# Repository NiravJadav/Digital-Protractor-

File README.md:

# Digital-Protractor-
What if Your Ruler Scale converted in to Protractor .....  This Project is all about convert an ordinary ruler in to Smart Ruler having a extra feature of measurement of Angle.

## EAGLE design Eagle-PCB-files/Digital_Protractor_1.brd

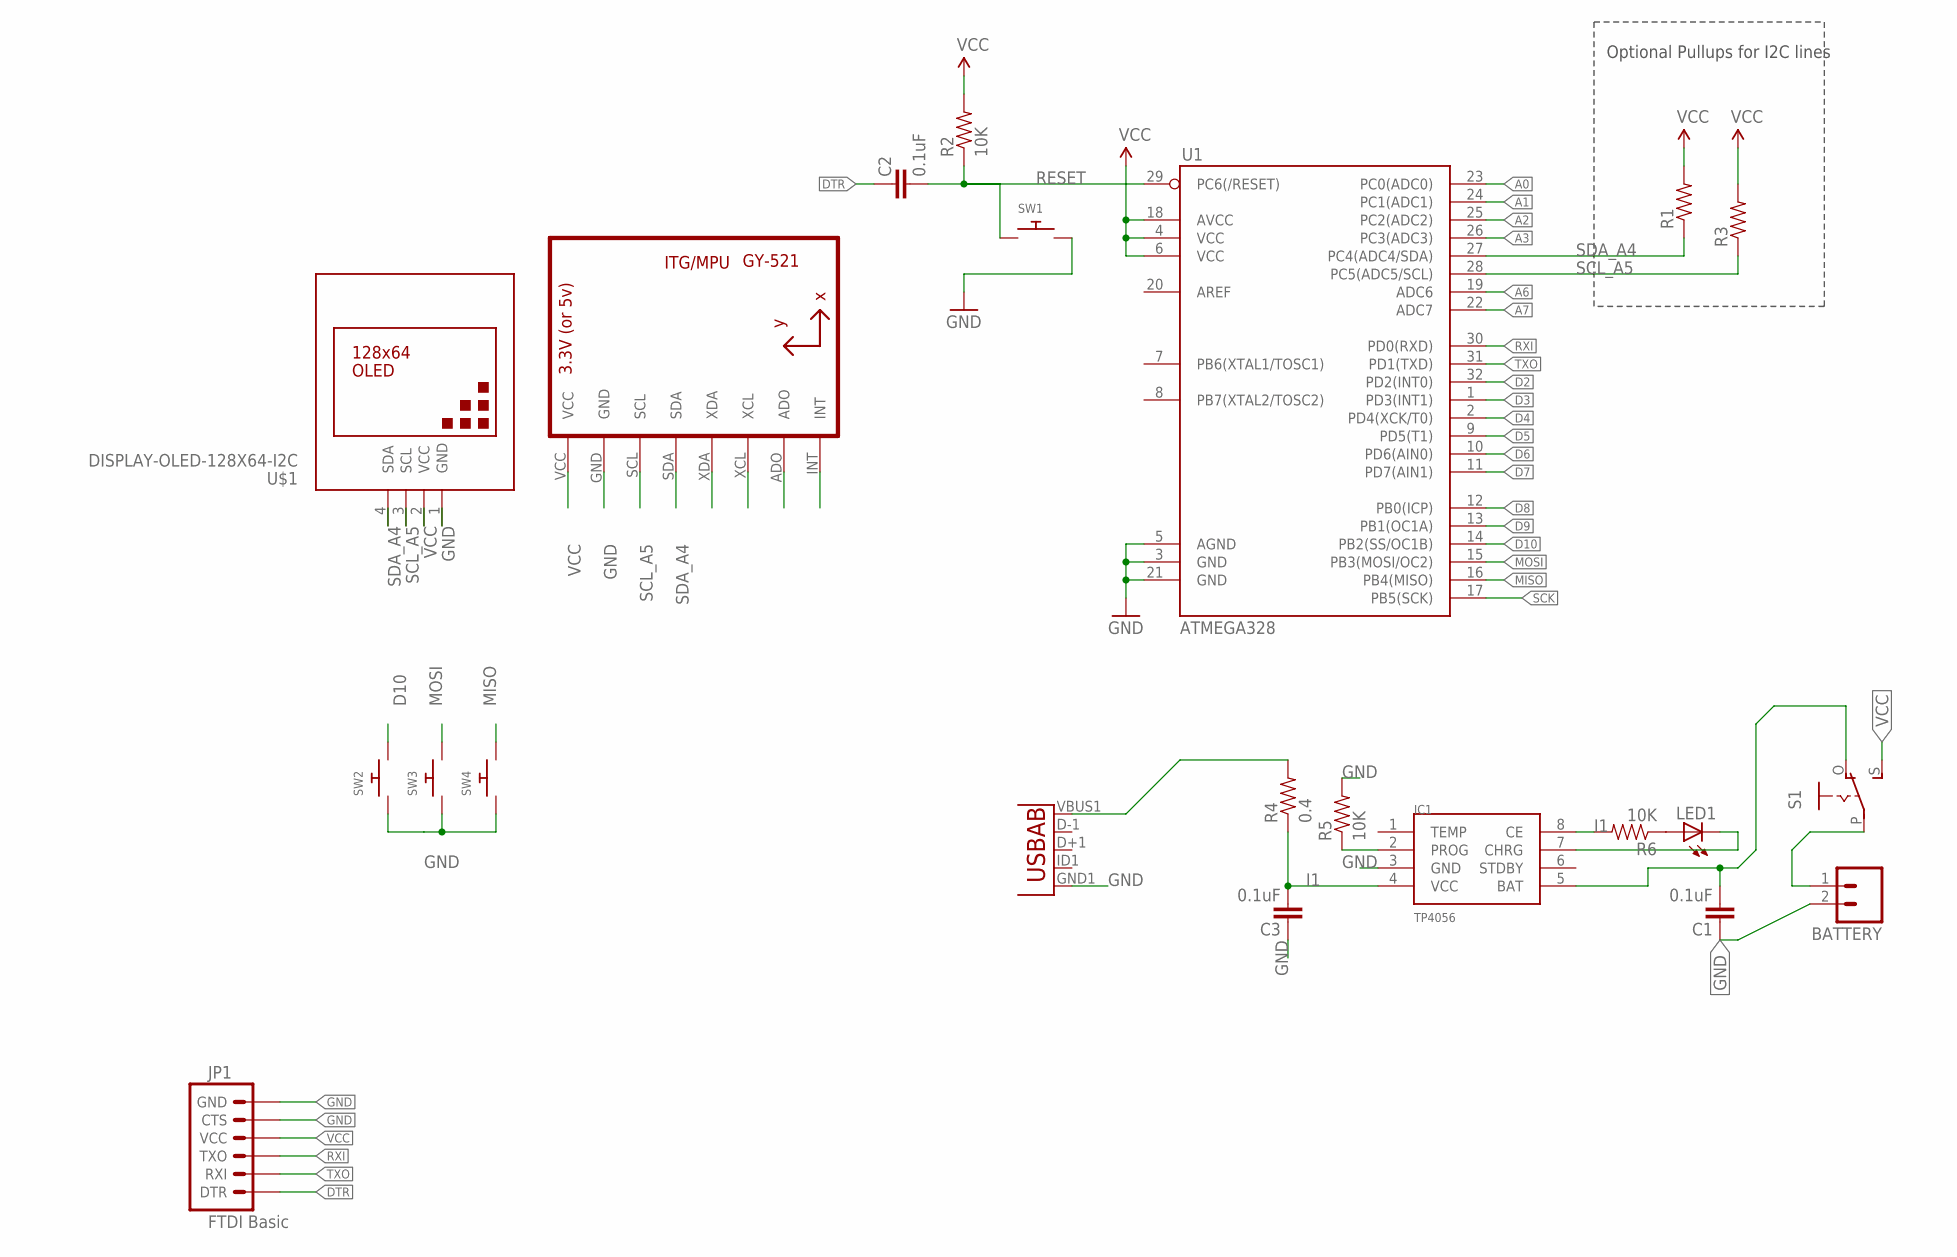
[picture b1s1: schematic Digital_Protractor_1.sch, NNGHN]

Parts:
BATTERY: M02PTH; 1X02
C1, C2, C3: 0.1uF; 0603-CAP
IC1: TP4056; SOP-8
JP1: FTDI Basic; 1X06
LED1: LED; SMARTLED-TTW
R1, R3: RESISTOR0603-RES; 0603-RES
R2, R5, R6: 10K; 0603-RES
R4: 0.4; 0603-RES
S1: EG1218S; EG1218
SW1: SWITCH_PUSHBUTTONEVQ-PE; TACT_PANA-EVQ
SW2, SW3, SW4: SWITCH_PUSHBUTTONSOFTTOUCHSMD_SJ; PUSHBUTTON_SMD_SJ
U1: ATMEGA328; TQFP32-08
U2: GY-521MPU6050; GY-521
U3: USB""; USB-MICRO-SMD
U$1: DISPLAY-OLED-128X64-I2C

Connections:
A0: U1.23 (PC0(ADC0))
A1: U1.24 (PC1(ADC1))
A2: U1.25 (PC2(ADC2))
A3: U1.26 (PC3(ADC3))
A6: U1.19 (ADC6)
A7: U1.22 (ADC7)
D2: U1.32 (PD2(INT0))
D3: U1.1 (PD3(INT1))
D4: U1.2 (PD4(XCK/T0))
D5: U1.9 (PD5(T1))
D6: U1.10 (PD6(AIN0))
D7: U1.11 (PD7(AIN1))
D8: U1.12 (PB0(ICP))
D9: U1.13 (PB1(OC1A))
D10: SW2.P$2, U1.14 (PB2(SS/OC1B))
DTR: C2.2, JP1.1 (DTR)
GND: BATTERY.2, C1.2, C3.2, IC1.3 (GND), JP1.5 (CTS), JP1.6 (GND), R5.2, SW1.P$2, SW2.P$1, SW3.P$1, SW4.P$1, U1.3 (GND), U1.5 (AGND), U1.21 (GND), U2.GND, U3.GND1 (GND), U$1.1 (GND)
I1: C3.1, IC1.4 (VCC), IC1.8 (CE), R4.1, R6.2
MISO: SW4.P$2, U1.16 (PB4(MISO))
MOSI: SW3.P$2, U1.15 (PB3(MOSI/OC2))
unnamed: IC1.2 (PROG), R5.1
unnamed: LED1.A@1 (A), R6.1
unnamed: IC1.7 (CHRG), LED1.C@1 (C)
unnamed: C1.1, IC1.5 (BAT), S1.O
unnamed: R4.2, U3.VBUS1 (VBUS)
unnamed: BATTERY.1, S1.P
RESET: C2.1, R2.1, SW1.P$1, U1.29 (PC6(/RESET))
RXI: JP1.3 (TXO), U1.30 (PD0(RXD))
SCK: U1.17 (PB5(SCK))
SCL_A5: R3.1, U1.28 (PC5(ADC5/SCL)), U2.SCL, U$1.3 (SCL)
SDA_A4: R1.1, U1.27 (PC4(ADC4/SDA)), U2.SDA, U$1.4 (SDA)
TXO: JP1.2 (RXI), U1.31 (PD1(TXD))
VCC: JP1.4 (VCC), R1.2, R2.2, R3.2, S1.S, U1.4 (VCC), U1.6 (VCC), U1.18 (AVCC), U2.VCC, U$1.2 (VCC)

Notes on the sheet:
Optional Pullups for I2C lines

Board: 2 copper layers, 22 parts (2 on the bottom side), 18 nets, no tracks yet.

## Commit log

2019-02-22 Arduino Design file
2019-02-22 digital protractor
2019-02-22 Create aqw
2019-02-22 Create a

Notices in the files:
parts and their libraries:
diy-modules: Released under the Creative Commons Attribution 4.0 International License: http://creativecommons.org/licenses/by/4.0
